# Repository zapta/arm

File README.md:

ARM PROJECTS
============

ARM PRO MINI 

Files: https://github.com/zapta/arm/tree/master/pro-mini

Documentation: https://github.com/zapta/arm/tree/master/pro-mini#arm-pro-mini

PHONE FINDER

Files: https://github.com/zapta/arm/tree/master/phone-finder

Documentation: https://github.com/zapta/arm/tree/master/phone-finder#phone-finder

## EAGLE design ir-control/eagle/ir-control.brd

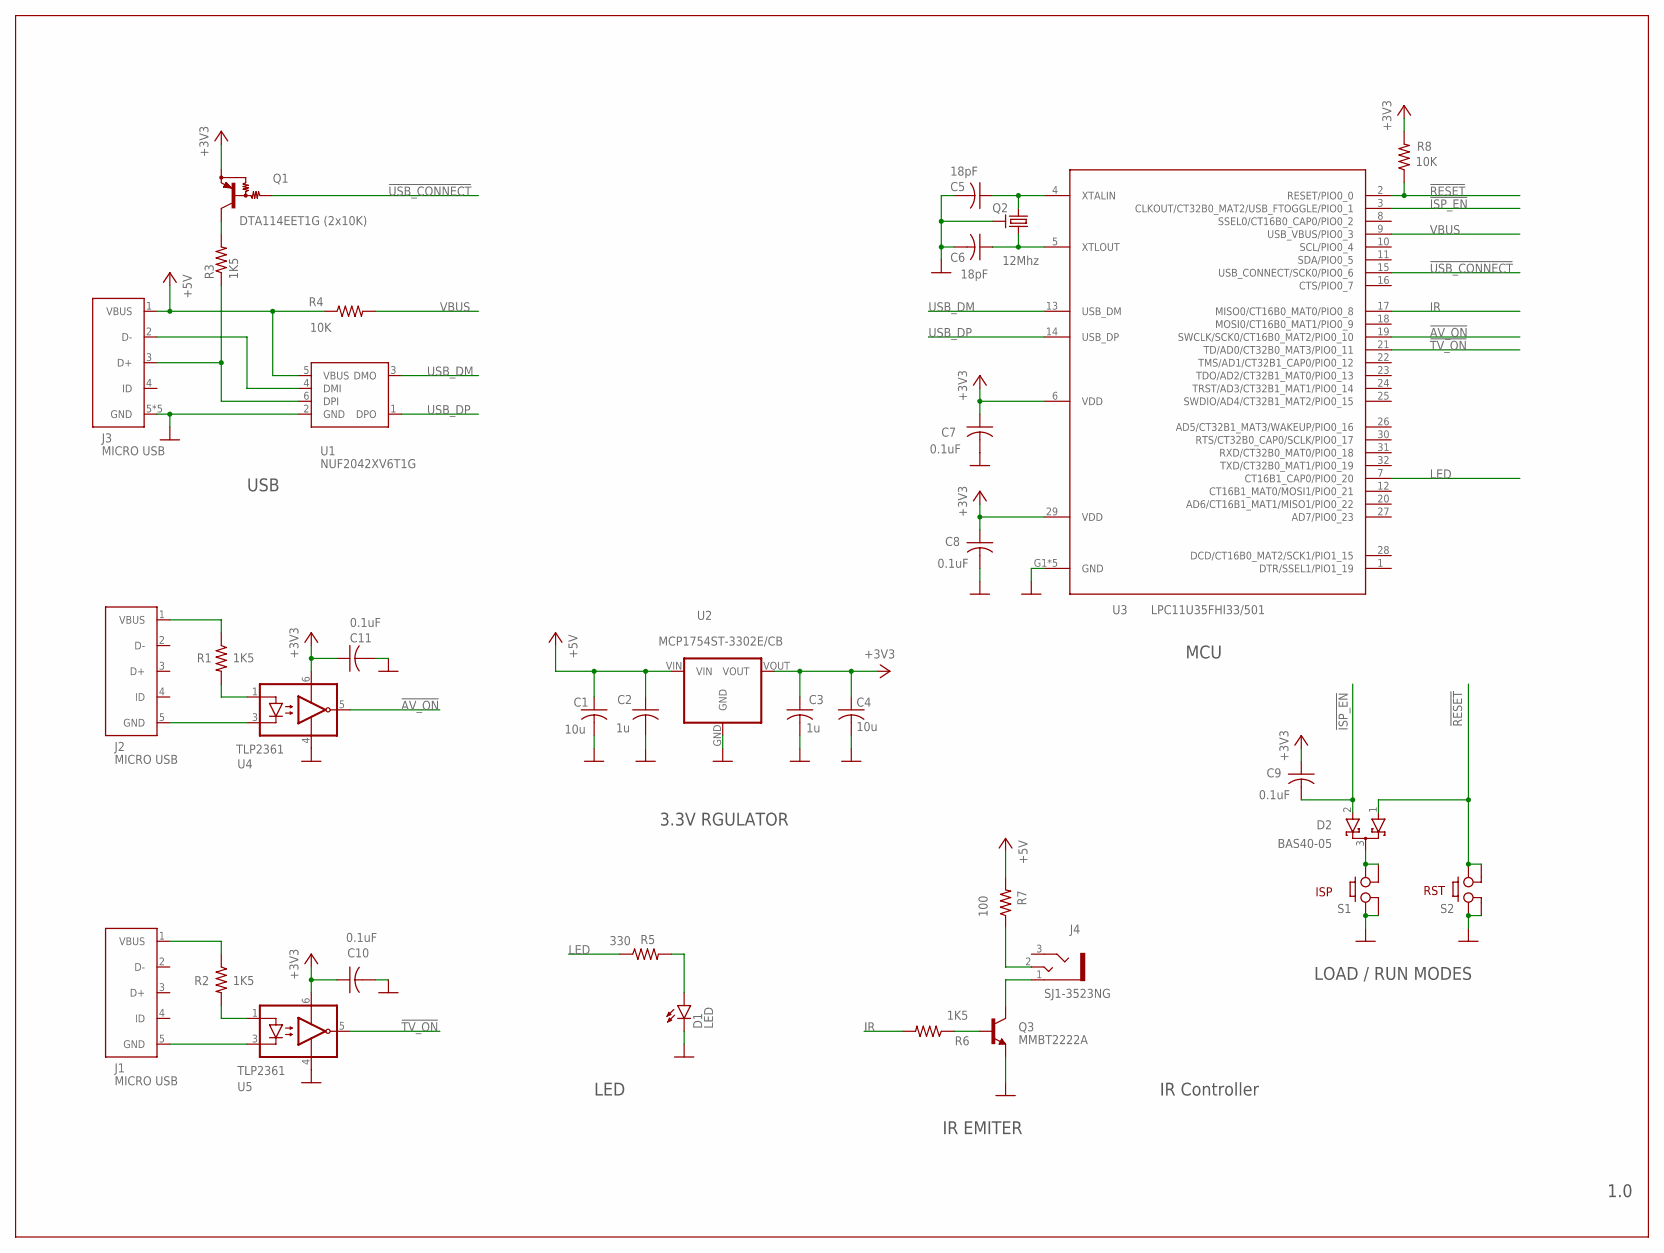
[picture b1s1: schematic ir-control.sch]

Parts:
C1, C4: 10u; C0805K
C2, C3: 1u; C0603K
C5, C6: 18pF; C0402K
C7, C8, C9, C10, C11: 0.1uF; C0402K
D1: LED
D2: BAS40-05; SOT23
J1, J2, J3: MICRO USB; USB-MICRO
J4: SJ1-3523NG; JACK
Q1: DTA114EET1G (2x10K); SC75-BEC
Q2: 12Mhz; CRYSTAL
Q3: MMBT2222A; SOT23
R1, R2, R3, R6: 1K5; R0402
R4, R8: 10K; R0402
R5: 330; R0402
R7: 100; R0402
S1: CKN10502CT-ND; PUSH_BUTTON
S2: PUSH-BUTTON; PUSH_BUTTON
U1: NUF2042XV6T1G; SOT-563
U2: MCP1754ST-3302E/CB; SOT-23A
U3: LPC11U35FHI33/501; HVQFN33-5MM
U4, U5: TLP2361; SO6

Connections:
!AV_ON: U3.19 (SWCLK/SCK0/CT16B0_MAT2/PIO0_10), U4.5 (OUT)
!ISP_EN: C9.2, D2.2 (A2), U3.3 (CLKOUT/CT32B0_MAT2/USB_FTOGGLE/PIO0_1)
!RESET: D2.1 (A1), R8.1, S2.B1, S2.B1P (B1), S2.B2, S2.B2P (B2), U3.2 (RESET/PIO0_0)
!TV_ON: U3.21 (TD/AD0/CT32B0_MAT3/PIO0_11), U5.5 (OUT)
!USB_CONNECT: Q1.B, U3.15 (USB_CONNECT/SCK0/PIO0_6)
+3V3: C3.1, C4.1, C7.1, C8.1, C9.1, C10.1, C11.1, Q1.E, R8.2, U2.VOUT, U3.6 (VDD), U3.29 (VDD), U4.6 (VCC), U5.6 (VCC)
+5V: C1.1, C2.1, J3.1 (VBUS), R4.1, R7.2, U1.5 (VBUS), U2.VIN
GND: C1.2, C2.2, C3.2, C4.2, C5.2, C6.2, C7.2, C8.2, C10.2, C11.2, D1.K (C), J3.5 (GND), J3.G1 (GND), J3.G2 (GND), J3.G3 (GND), J3.G4 (GND), Q2.2 (GND), Q2.4 (GND), Q3.2 (E), S1.A1, S1.A1P (A1), S1.A2, S1.A2P (A2), S2.A1, S2.A1P (A1), S2.A2, S2.A2P (A2), U1.2 (GND), U2.GND, U3.G1 (GND), U3.G2 (GND), U3.G3 (GND), U3.G4 (GND), U3.TAB (GND), U4.4 (GND), U5.4 (GND)
IR: R6.2, U3.17 (MISO0/CT16B0_MAT0/PIO0_8)
LED: R5.1, U3.7 (CT16B1_CAP0/PIO0_20)
unnamed: C5.1, Q2.3 (2), U3.4 (XTALIN)
unnamed: J2.1 (VBUS), R1.1
unnamed: C6.1, Q2.1, U3.5 (XTLOUT)
unnamed: Q3.1 (B), R6.1
unnamed: Q1.C, R3.2
unnamed: J3.3 (D+), R3.1, U1.6 (DPI)
unnamed: J1.1 (VBUS), R2.1
unnamed: J4.1, Q3.3 (C)
unnamed: J4.2, R7.1
unnamed: J2.5 (GND), U4.3 (C)
unnamed: J1.5 (GND), U5.3 (C)
unnamed: J3.2 (D-), U1.4 (DMI)
unnamed: R2.2, U5.1 (A)
unnamed: D1.A, R5.2
unnamed: R1.2, U4.1 (A)
unnamed: D2.3 (C), S1.B1, S1.B1P (B1), S1.B2, S1.B2P (B2)
USB_DM: U1.3 (DMO), U3.13 (USB_DM)
USB_DP: U1.1 (DPO), U3.14 (USB_DP)
VBUS: R4.2, U3.9 (USB_VBUS/PIO0_3)

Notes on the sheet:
IR Controller
1.0
USB
MCU
ISP
RST
3.3V RGULATOR
LOAD / RUN MODES
LED
IR EMITER

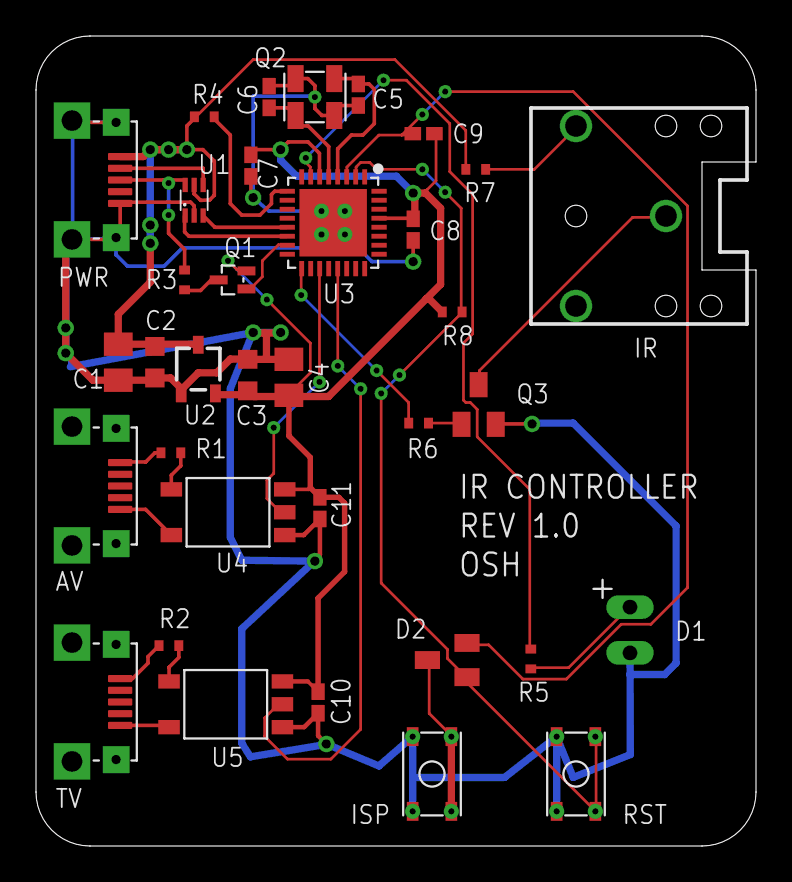
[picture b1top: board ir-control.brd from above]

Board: 2 copper layers, 40.0 x 45.0 mm, 35 parts (0 on the bottom side), 29 nets.

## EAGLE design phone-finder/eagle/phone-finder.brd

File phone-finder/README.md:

ARM PRO MINI
============

### OVERVIEW

Phone Finder is simple system that allows familty members to locate their cell phones.
The system works with an arbitrary number of Amazon Dash buttons that are placed 
in key locations such as near the exit door. When a Dash button is pressed, the system
dials the phone number that associated with that button, causing the respective cell
phone to ring.

The system uses a Phone Finder box that bridges between the Wifi connections from
the Dash buttons and the phone landline cord. The Phone Finder box acts as a Wifi 
access point that accepts Wifi connections directly from the Dash buttons and does
no require a local Wifi network or a connection to the internet.

[Schematic (PDF)](https://github.com/zapta/arm/blob/master/phone-finder/eagle/phone-finder-schematic.pdf)

This design is in the public domain and is provided AS IS. I am not an electronic or telephony engineer. All source files including eagle, LPCXpresso project, C++ source files and openscad 3D model source files are included.

<br>

### Design notes (assorted order)

* The PCB include an ARM mcu, a Wifi module and a phone line dialer. 
* The MCU design is based on the Arm Pro Mini. 
* The firmware is mbed based and was developed using NPX LPCXpresso (see ARM Pro Mini documentation)
* Loading the firmaware is done via the USB connector, similar to ARM Pro Mini.
* The enclosure and the LED mount are 3D printed. STL files and openscad source files are availabe here.
* To change the phone numbers you will need change the source files and build. Currntly there is no soft EEPROM based configuration.
* The DTFM is generated using two 16 bit counters of the ARM MCU. They generate square waves that are filtered out by a simple RC filter, the coupling transformer and the phone line itself.
* For simplicty, the coupling transformer was not decoupled from DC on both its primary and secondary. Howerver, it seems to work well.
* When assembling the PCB, the orientation of the transformer does matter. Make sure the primary is at the PCB side marked with 'P'.
* If you want to experiment talking directly to the wifi module, build and load the wifi-serial project. This will make the MCU acting as a USB to serial (CDC) adapter.
* For antenna I just soldered a 2$ AWG solid wire (strip at the end for the solder joint). If you want to experiment with different antennas, you can use the wifi module's s/n figure to compare configurations (use the serial-wifi firmware above).
* The PCB is attached to the enclosure base using Scotch Mounting Tape.
* The firmware comes with the default AP SSID 'dashrx' and the password 'dashdash' (password must have at least 8 chars). Change the firmware to customize.
* To make a button connecting to the AP, first set it with a real wifi AP connected to the internet. Set its SSID and password to the ones you want to use, and perform the Amazon Dash button setting using that real AP. Abort the process at the point where you need to select a product. Make sure to change the SSID of the real AP to other than your SSID of choice such that it doesn't interfer with the phone finder.
* Once your button(s) connect successuly to your phone finder (connect the USB connector to a computer, the phone finder acts as a  CDC serial port and dumps diagnostic data), add the mac address of those buttons to the button table in the firmware. 

<br>

If I will find time, I plan to design a lower cost version of the Phone Finder, replacing the ARM mcu and Wifi Module with an ESP8266/Arduino.

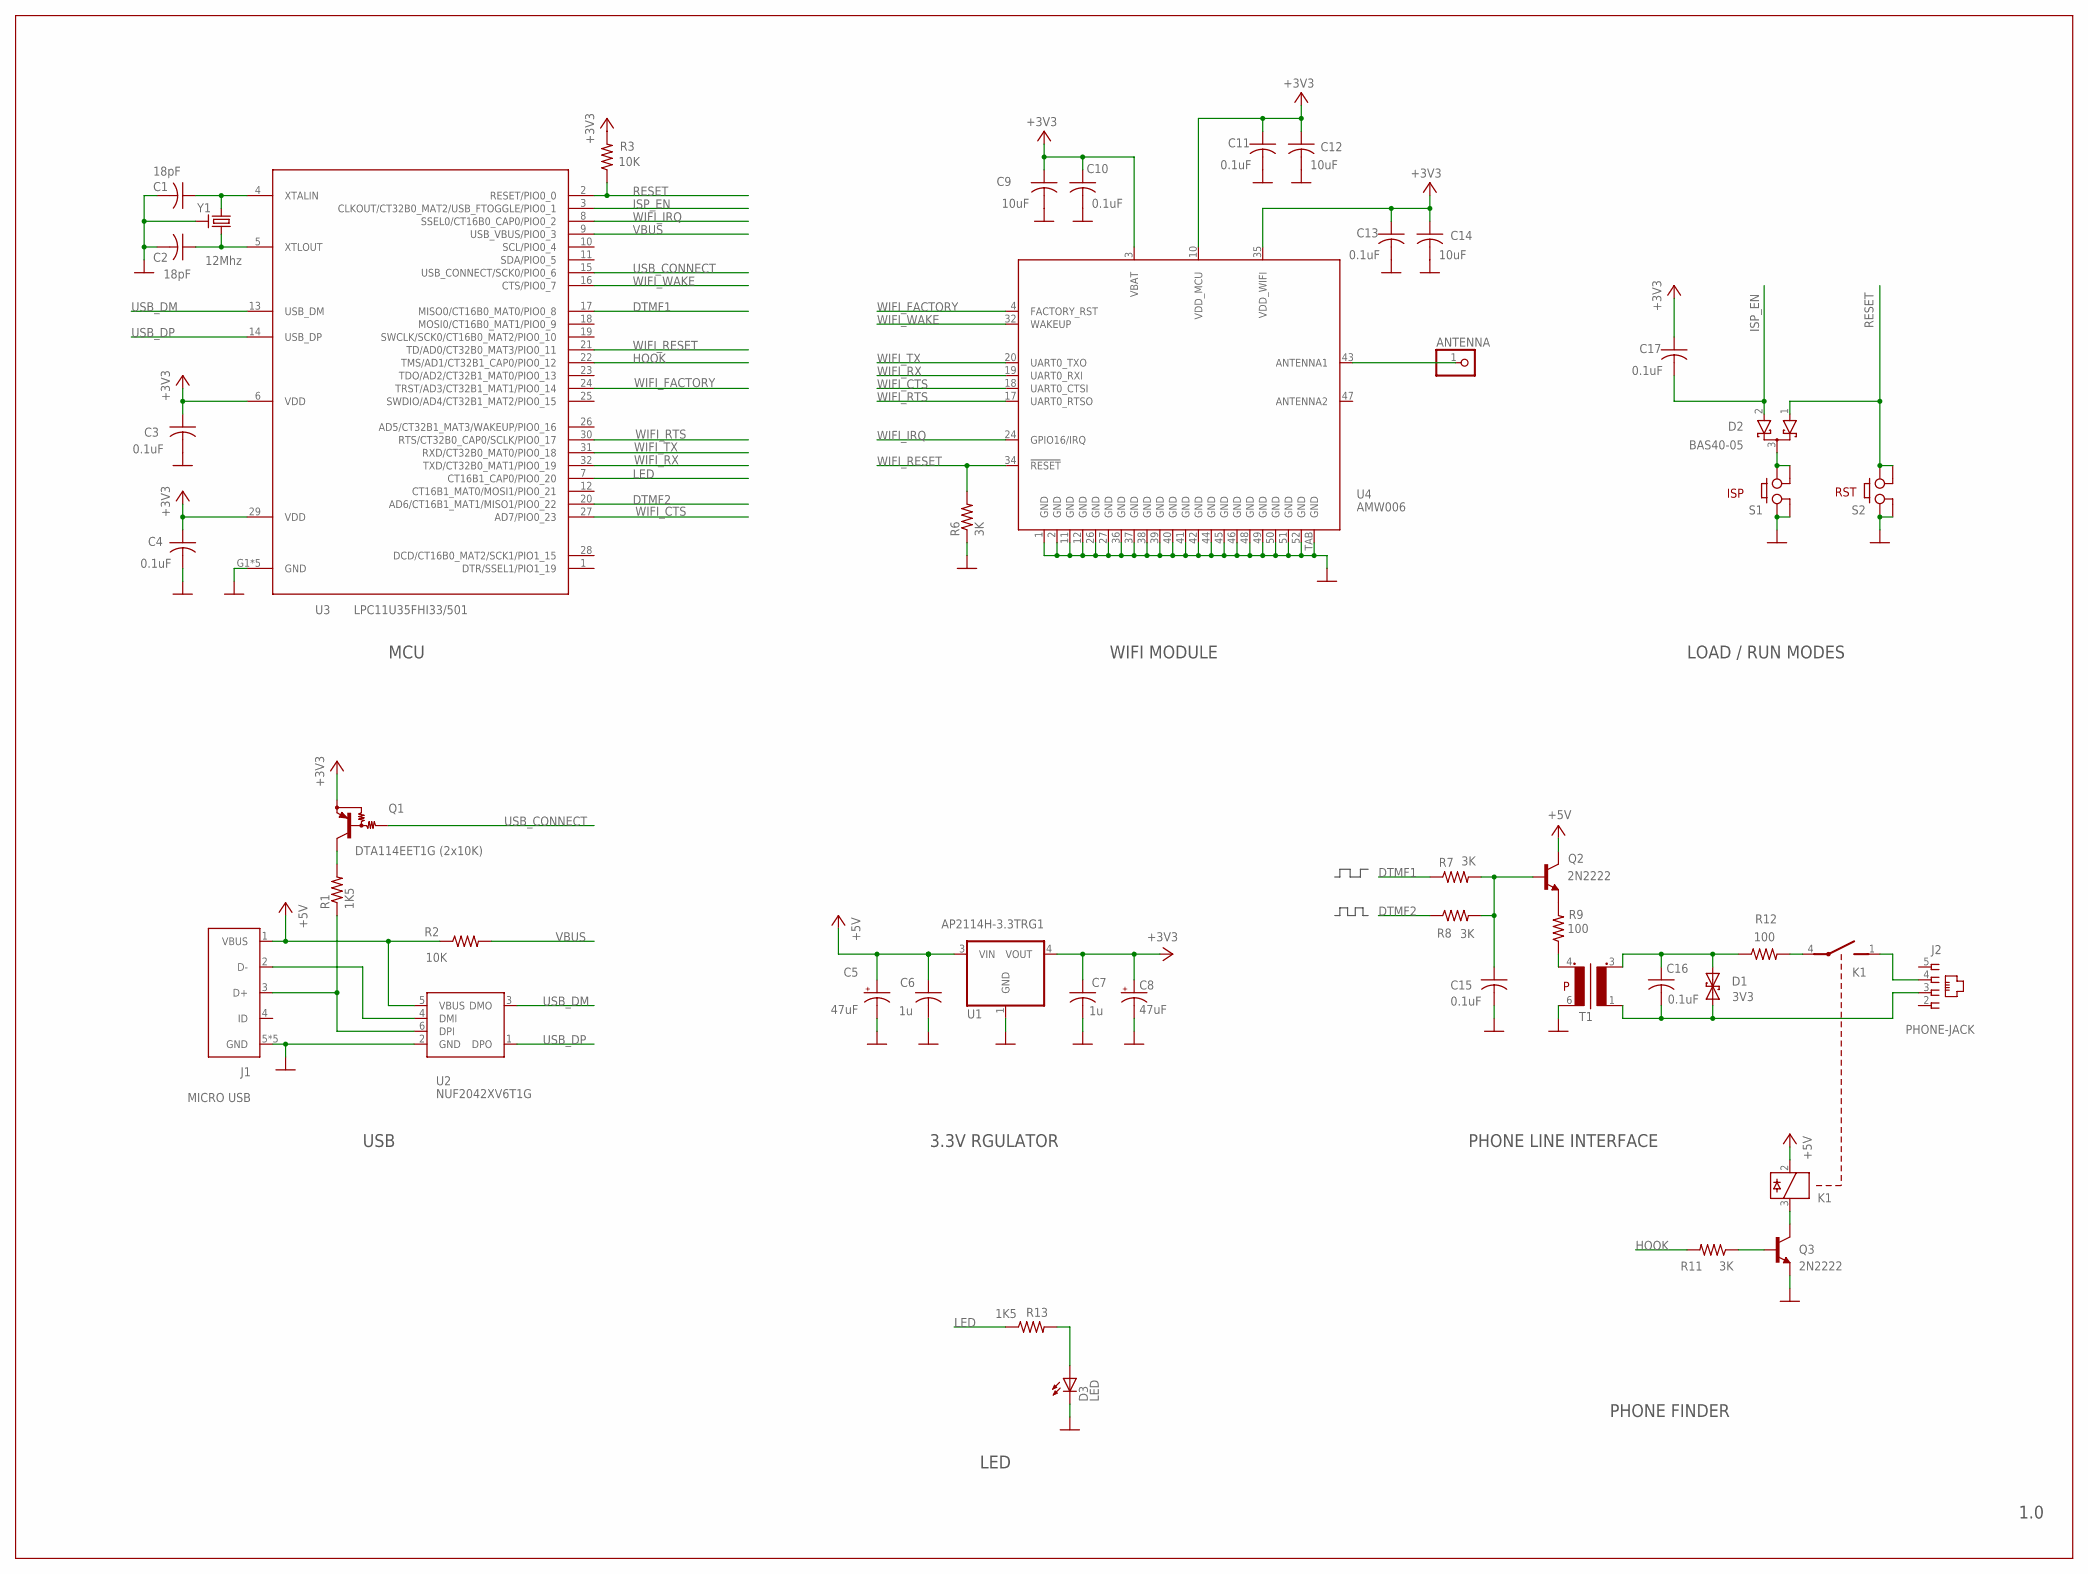
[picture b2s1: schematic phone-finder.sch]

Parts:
ANTENNA: PINHD-1X1
C1, C2: 18pF; C0402K
C3, C4, C10, C11, C13, C15, C16, C17: 0.1uF; C0402K
C5, C8: 47uF; UD-6,3X5,8_NICHICON
C6, C7: 1u; C0603K
C9, C12, C14: 10uF; C0805K
D1: 3V3; DZ-0402
D2: BAS40-05; SOT23
D3: LED
J1: MICRO USB; USB-MICRO
J2: PHONE-JACK
K1: RELAY
Q1: DTA114EET1G (2x10K); SC75-BEC
Q2, Q3: 2N2222; SOT23
R1, R13: 1K5; R0402
R2, R3: 10K; R0402
R6, R7, R8, R11: 3K; R0402
R9, R12: 100; R0805
S1, S2: PUSH-BUTTON; PUSH_BUTTON
T1: TRANSFORMER
U1: AP2114H-3.3TRG1; SOT223
U2: NUF2042XV6T1G; SOT-563
U3: LPC11U35FHI33/501; HVQFN33-5MM
U4: AMW006; WIFI_MODULE
Y1: 12Mhz; CRYSTAL

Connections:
+3V3: C3.1, C4.1, C7.1, C8.+, C9.1, C10.1, C11.1, C12.1, C13.1, C14.1, C17.1, Q1.E, R3.2, U1.4 (VOUT), U3.6 (VDD), U3.29 (VDD), U4.3 (VBAT), U4.10 (VDD_MCU), U4.35 (VDD_WIFI)
+5V: C5.+, C6.1, J1.1 (VBUS), K1.2 (COIL-POS), Q2.3 (C), R2.1, U1.3 (VIN), U2.5 (VBUS)
DTMF1: R7.1, U3.17 (MISO0/CT16B0_MAT0/PIO0_8)
DTMF2: R8.1, U3.20 (AD6/CT16B1_MAT1/MISO1/PIO0_22)
GND: C1.2, C2.2, C3.2, C4.2, C5.-, C6.2, C7.2, C8.-, C9.2, C10.2, C11.2, C12.2, C13.2, C14.2, C15.2, D3.K (C), J1.5 (GND), J1.G1 (GND), J1.G2 (GND), J1.G3 (GND), J1.G4 (GND), Q3.2 (E), R6.1, S1.A1, S1.A1P (A1), S1.A2, S1.A2P (A2), S2.A1, S2.A1P (A1), S2.A2, S2.A2P (A2), T1.6 (P2), U1.1 (GND), U2.2 (GND), U3.G1 (GND), U3.G2 (GND), U3.G3 (GND), U3.G4 (GND), U3.TAB (GND), U4.1 (GND), U4.2 (GND), U4.11 (GND), U4.12 (GND), U4.26 (GND), U4.27 (GND), U4.36 (GND), U4.37 (GND), U4.38 (GND), U4.39 (GND), U4.40 (GND), U4.41 (GND), U4.42 (GND), U4.44 (GND), U4.45 (GND), U4.46 (GND), U4.48 (GND), U4.49 (GND), U4.50 (GND), U4.51 (GND), U4.52 (GND), U4.TAB (GND), Y1.2 (GND), Y1.4 (GND)
HOOK: R11.2, U3.22 (TMS/AD1/CT32B1_CAP0/PIO0_12)
ISP_EN: C17.2, D2.2 (A2), U3.3 (CLKOUT/CT32B0_MAT2/USB_FTOGGLE/PIO0_1)
LED: R13.1, U3.7 (CT16B1_CAP0/PIO0_20)
unnamed: C1.1, U3.4 (XTALIN), Y1.3 (2)
unnamed: ANTENNA.1, U4.43 (ANTENNA1)
unnamed: C2.1, U3.5 (XTLOUT), Y1.1
unnamed: K1.3 (COIL-NEG), Q3.3 (C)
unnamed: Q1.C, R1.2
unnamed: J1.3 (D+), R1.1, U2.6 (DPI)
unnamed: Q3.1 (B), R11.1
unnamed: Q2.2 (E), R9.2
unnamed: C16.1, D1.2, R12.1, T1.3 (S1)
unnamed: C16.2, D1.1, J2.3, T1.1 (S2)
unnamed: J2.4, K1.1 (S1)
unnamed: J1.2 (D-), U2.4 (DMI)
unnamed: D3.A, R13.2
unnamed: K1.4 (S2), R12.2
unnamed: D2.3 (C), S1.B1, S1.B1P (B1), S1.B2, S1.B2P (B2)
unnamed: R9.1, T1.4 (P1)
unnamed: C15.1, Q2.1 (B), R7.2, R8.2
RESET: D2.1 (A1), R3.1, S2.B1, S2.B1P (B1), S2.B2, S2.B2P (B2), U3.2 (RESET/PIO0_0)
USB_CONNECT: Q1.B, U3.15 (USB_CONNECT/SCK0/PIO0_6)
USB_DM: U2.3 (DMO), U3.13 (USB_DM)
USB_DP: U2.1 (DPO), U3.14 (USB_DP)
VBUS: R2.2, U3.9 (USB_VBUS/PIO0_3)
WIFI_CTS: U3.27 (AD7/PIO0_23), U4.18 (UART0_CTSI)
WIFI_FACTORY: U3.24 (TRST/AD3/CT32B1_MAT1/PIO0_14), U4.4 (FACTORY_RST)
WIFI_IRQ: U3.8 (SSEL0/CT16B0_CAP0/PIO0_2), U4.24 (GPIO16/IRQ)
WIFI_RESET: R6.2, U3.21 (TD/AD0/CT32B0_MAT3/PIO0_11), U4.34 (!RESET)
WIFI_RTS: U3.30 (RTS/CT32B0_CAP0/SCLK/PIO0_17), U4.17 (UART0_RTSO)
WIFI_RX: U3.32 (TXD/CT32B0_MAT1/PIO0_19), U4.19 (UART0_RXI)
WIFI_TX: U3.31 (RXD/CT32B0_MAT0/PIO0_18), U4.20 (UART0_TXO)
WIFI_WAKE: U3.16 (CTS/PIO0_7), U4.32 (WAKEUP)

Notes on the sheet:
PHONE FINDER
1.0
USB
MCU
ISP
RST
3.3V RGULATOR
LOAD / RUN MODES
WIFI MODULE
PHONE LINE INTERFACE
LED

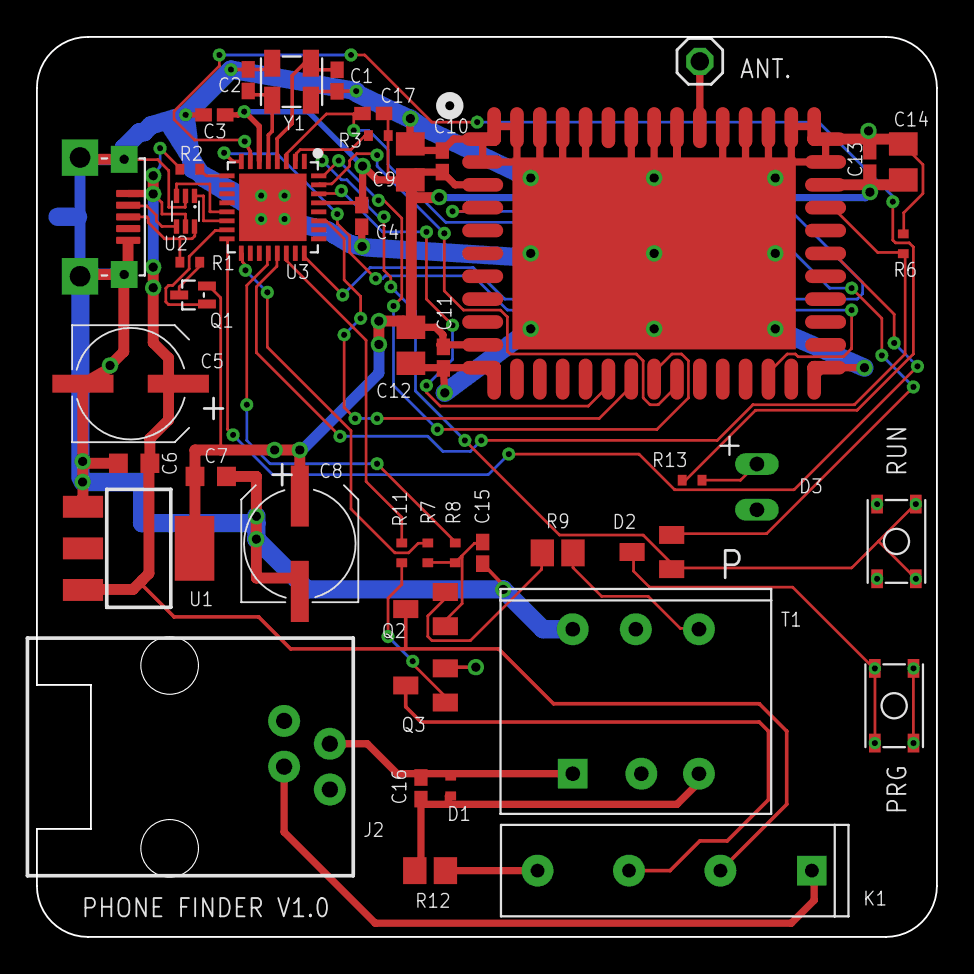
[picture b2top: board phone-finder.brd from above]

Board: 2 copper layers, 50.0 x 50.0 mm, 45 parts (0 on the bottom side), 38 nets.

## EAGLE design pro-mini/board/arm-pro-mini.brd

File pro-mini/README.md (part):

ARM PRO MINI
============

### OVERVIEW

ARM PRO MINI is a small barebone open source ARM M0 microcontroller board that is great for 
quick prototyping and as a starting point for your own ARM based custom designs. 
It was designed and named after the venerable Arduino Pro Mini and it is an excellent 
stepping stone for makers and hobbyists 'graduating' from Arduino to the ARM architecture.

[Schematic (PDF)](https://github.com/zapta/arm/blob/master/pro-mini/board/arm-pro-mini-schematic.pdf)

[BOM (CSV)](https://github.com/zapta/arm/blob/master/pro-mini/board/arm-pro-mini-bom.csv)

<br>
### Highlights

* Prototyping friendly. Compatible with standard soldieries breadboards and can be soldered to a standard 0.1” proto board.
* Straight forward barebone design. Customize for your own PCB design by selecting the portions of the circuit you need.
* Single package install of the free and fully feature IDE (NXP Eclipse/LPCXpresso).
* Zero software installation when using with the mbed.org online IDE.
* Full support of Windows, Mac OSX and Linux.
* Easy firmware upgrade using a file drag and drop. Programmers and adapters are not required, even if you are bringing up your own board!
* Supports optional debuggers (such as [LPC-LINK 2](http://www.digikey.com/short/7nr7n4)) for single stepping and full debugging capabilities.
* I/O library and a hello world example (with serial printing over USB, parallel port io, blinking LED, and timing).
* No-nonsense open source license (no commercial restrictions, sharing and attribution not required).

<br>
### Specification

Attribute | Value
:--------- | :-----
MCU | NXP ARM M0 LPC11U35FHI33/501
Memory | 64K flash, 8K RAM, 4K EEPROM
Speed | 48Mhz
Core voltage | 3.3V   (3.3V LDO included)
MCU Package | QFN 5x5mm, 0.5mm pitch, 32 pads + ground tab.
PCB dimensions | 1.5” x 0.775”  (38.1mm x 19.7mm)
PCB Layers | 2
PCB Thickness | 1mm recommended. (standard 1.6mm is also OK).
PCB file format | Eagle + PDF + Gerber files.
PCB rules | 6mil min trace, 7mil min spacing.
SMT Technology | 0402, QFN 0.5mm pitch.
Power options | USB, ext 3.3v, ext 16V max (with included 3.3V LDO) 
Header pins | 2x15 DIP, 0.7” row spacing. Access to all MCU's I/O pins.
USB Connector | Micro B
Debugger Connector | SWD 2x5 pin header, 0.5” pitch
Crystal | 12Mhz (for 48Mhz MCU operation).
LEDS | Power (blue), USB status (green), Application (red), 
Switches | Reset, ISP.
Recomanded IDE | NXP LPCXpresso (eclipse based, free)

<br>
### Pinout Diagram

<br>
### Where To Get an ARM PRO MINI?
As of Jan 2014 I have a limited supply of free ARM PRO MINI samples that I am giving to established eevblog users.
Since the license of the ARM PRO MINI is very liberal (attribution and share alike not required, commercial mixing and cloning are ok and free) it is likely that others will want to make them available to the public. If you want to list your offering here please let me know.

1. Make your own board. This will be a rewarding project, especially if you want to practice assembly of SMD boards. The complete BOM including digikey part numbers is available in the repository. You can order the PCB from OSH PARK by uploading the Eagle .brd file (~$6 per three boards). Mylar stencils are available from OSH STENCILS (I prefer the 5mil over the 3mil ones) and the board will be ready to use once it come out of your toaster oven (no need to program a bootloader). Make sure to have a decent magnifier glass for visutal inspection of the soldering and is you documented your build process let me know and I will mention it here. See more details below.

2. TBD.

<br>
### Quick Start 1 - Uploading a Compiled Program

This section will teach you how to load new firmware on your board. It is done by switching the board to the USB/ISP virtual disk mode and copying the new binary file.

1. Connect the ARM PRO MINI board to a USB port of a Max OSX, Linux or Windows computer.
2. Restart board in ISP mode by pressing the ISP button  (note: older versions require releasing the RST button while the ISP button is pressed).
3. The ARM PRO MINI will mount itself on your computer as an external disk with a single file named firmware.bin.
4. Copy one of the two provided hello world image files over the *firmware.bin* file. Note: on Mac OSX drag and drop does not work, instead using the cp shell command: *cp hello_world_fast_blink.bin "/Volumes/CRP DISABLD/firmware.bin"*
5. Press the RST button of the ARM PRO MINI to restart it in the RUN mode. The image file you just loaded should start running and the red LED on the ARM PRO MINI should blink.
6. Repeat the process with the other image file *hello_world_slow_blink.bin*  and notice how the blinking rate changes.

For more information about the USB bootloader see NXP's [application note AN11305](resources/lpc_bootloader/AN11305v.1.pdf).

<br>
### Quick Start 2 - Using the USB/Serial port.

This section will teach you how to view on your computer seial data output from the ARM PRO MINI. It is useful for example to communicate with a program running on the ARM PRO MINI or to debug a program you write using print messages.

1. Load and run a hello world image file as described above. Make sure the red LED blinks.
2. Identify the serial port on your computer. 
    * **Mac OSX:**  run _ls /dev/\*usb\*_, the port name looks like */dev/cu.usbmodemNXP-71*.
    * **Linux:** diff the output of the command _ls /dev/\*_ with and without the ARM PRO MINI 
      connected and look for a port that appears only when
      the ARM PRO MINI is connected. The serial port our linux test box is called */dev/ttyACM0* and is also availal with 
      two other name under the */dev/serial* directory.
    * **Windows:** (by Xenon Photon from the eevblog forums) 
      Identify the serial port on your computer: Open device manger, under "Ports(COM & LPT)" search for "LPC USB VCom Port (COMx)" 
      where x is the com port number.  
3. Use a terminal emulator to print the text received on the serial port you identified above.
    * **Mac OSX:** run the command *cat <port_name>*. For example *cat /dev/cu.usbmodemNXP-71*.
    * **Linux:** run the command *cat <port_name>*. For example *cat /dev/ttyACM0*.
    * **Windows:** (by Xenon Photon from the eevblog forums)
      Use a terminal emulator to print the text received on the serial port you identified above: 
      Download any terminal emulator, for example Tera Term http://en.sourceforge.jp/projects/ttssh2/releases/. 
      Select the com port of your device and click OK.
      Windows will install the required drive automatically via the internet. if the device was not recognized then 
      download the driver from here: http://www.lpcware.com/content/nxpfile/lpcxpresso-link2-usb-driver-package

The output will look like this:
~~~
...
Hello world: 4, 1500177
Hello world: 5, 1800178
Hello world: 6, 2100178
Hello world: 7, 2400178
Hello world: 8, 2700177
...
~~~

<br>
### Quick Start 3 - Installing the LPCXpresso IDE and compiling Hello World.

This section will teach you how to install the NXP LPCXpresso IDE and how to setup and compile a project for the ARM PRO MINI.

1. Download and Install the LPCXpresso IDE as described here http://www.lpcware.com/lpcxpresso/download. (this tutorial verified with LPCXpresso V7.3.0 on Mac OSX 10.9.5).
2. Copy the project directory https://github.com/zapta/arm/tree/master/pro-mini to your computer (e.g. by cloning the github repository or by extracting the zip file https://github.com/zapta/arm/archive/master.zip).
3. Import the *arm_pro_mini_lib* and *hellow_world* projects into LPCXpresso:
    * Select *File | Import... | General | Existing Projects into workspace* and then click *Next*
    * Select the archive file *arm_pro_min_getting_started.zip*, verify that the two projects *arm_pro_mini_lib* and *hello_world* are selected and then click *Finish*.
4. Build the hello world image file:
    * Right click on the *hello_world* project and select *Build Project*.
    * Expand the *hello_world* project and verify that the image file *hello_world.bin* created in the Debug directory.
7. Load the generated *hello_world.bin* image file to the ARM PRO MINI board using the USB/ISP bootloader as described above.
8. Modify the file *src/hello_file.cpp* in the *hellow_world* project (e.g. change the value of *kCycleTimeUsecs*), rebuild and load the file and verify that your changes took effect.

<br>

<br>
### Automatic Build/Download Using LPCXpresso
This section explains how to setup LPCXpresso to automate the process of building your project and downloading the generated .bin file to your ARM PRO MINI board via the USB/ISP bootloader (rather copying the .bin file manually as explained eariler). This is done by setting up the provided *arm_pro_mini_lib/tools/copy_bin_to_usb_isp.sh* script as an external LPCXpresso tool.

**New**: Batch file for Windows has been added. The existing script was tested on Mac OSX and should work also on Linux.

1. In LPCXpresson, open *Run | External Tools | External Tools Configuration ...*.
2. Add a new launch configuration.
3. Set the name of the new launch configuration to *USB_ISP*.
3. In the *Main* tab set the Location field to *${workspace_loc:/arm_pro_mini_lib/tools/copy_bin_to_usb_isp.sh}* on Mac; or to *${workspace_loc:/arm_pro_mini_lib/tools/copy_bin_to_usb_isp.bat}* on windows. Set the Arguments field to *${project_name} ${project_loc} ${config_name:${project_name}}*
4. In the *Common* tab check *External Tools* to display the external tool icon in the tool bar.
5. Click *Close*.
6. To build and download switch the ARM PRO MINI board to USB/ISP mode by pressing the ISP button (note: older versions of the board require release the RST button while the ISP button is pressed), then click on the *External Tool* icon and run USB/ISP. When the build and download are completed, reset your ARM PRO MINI board to start the new program you just downloaded.

<br>

<br>

<br>
### The ARM PRO MINI Library
This library includes everything you will need to program the ARM PRO MINI. It includes simplified low level chip and board definitions (based on LPCOPEN) as well as original code that support serial over USB/CDC, passive timers, digital pin I/O and more. It is installed in LPCXpresso as a library project which the hello world project (and in the future your own progrmas) depends on. The depenency is defined in the hello world LPCXpresso project such that compiling the hello world project also compiles the library if needed. 

<br>
### The Hello World Example
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
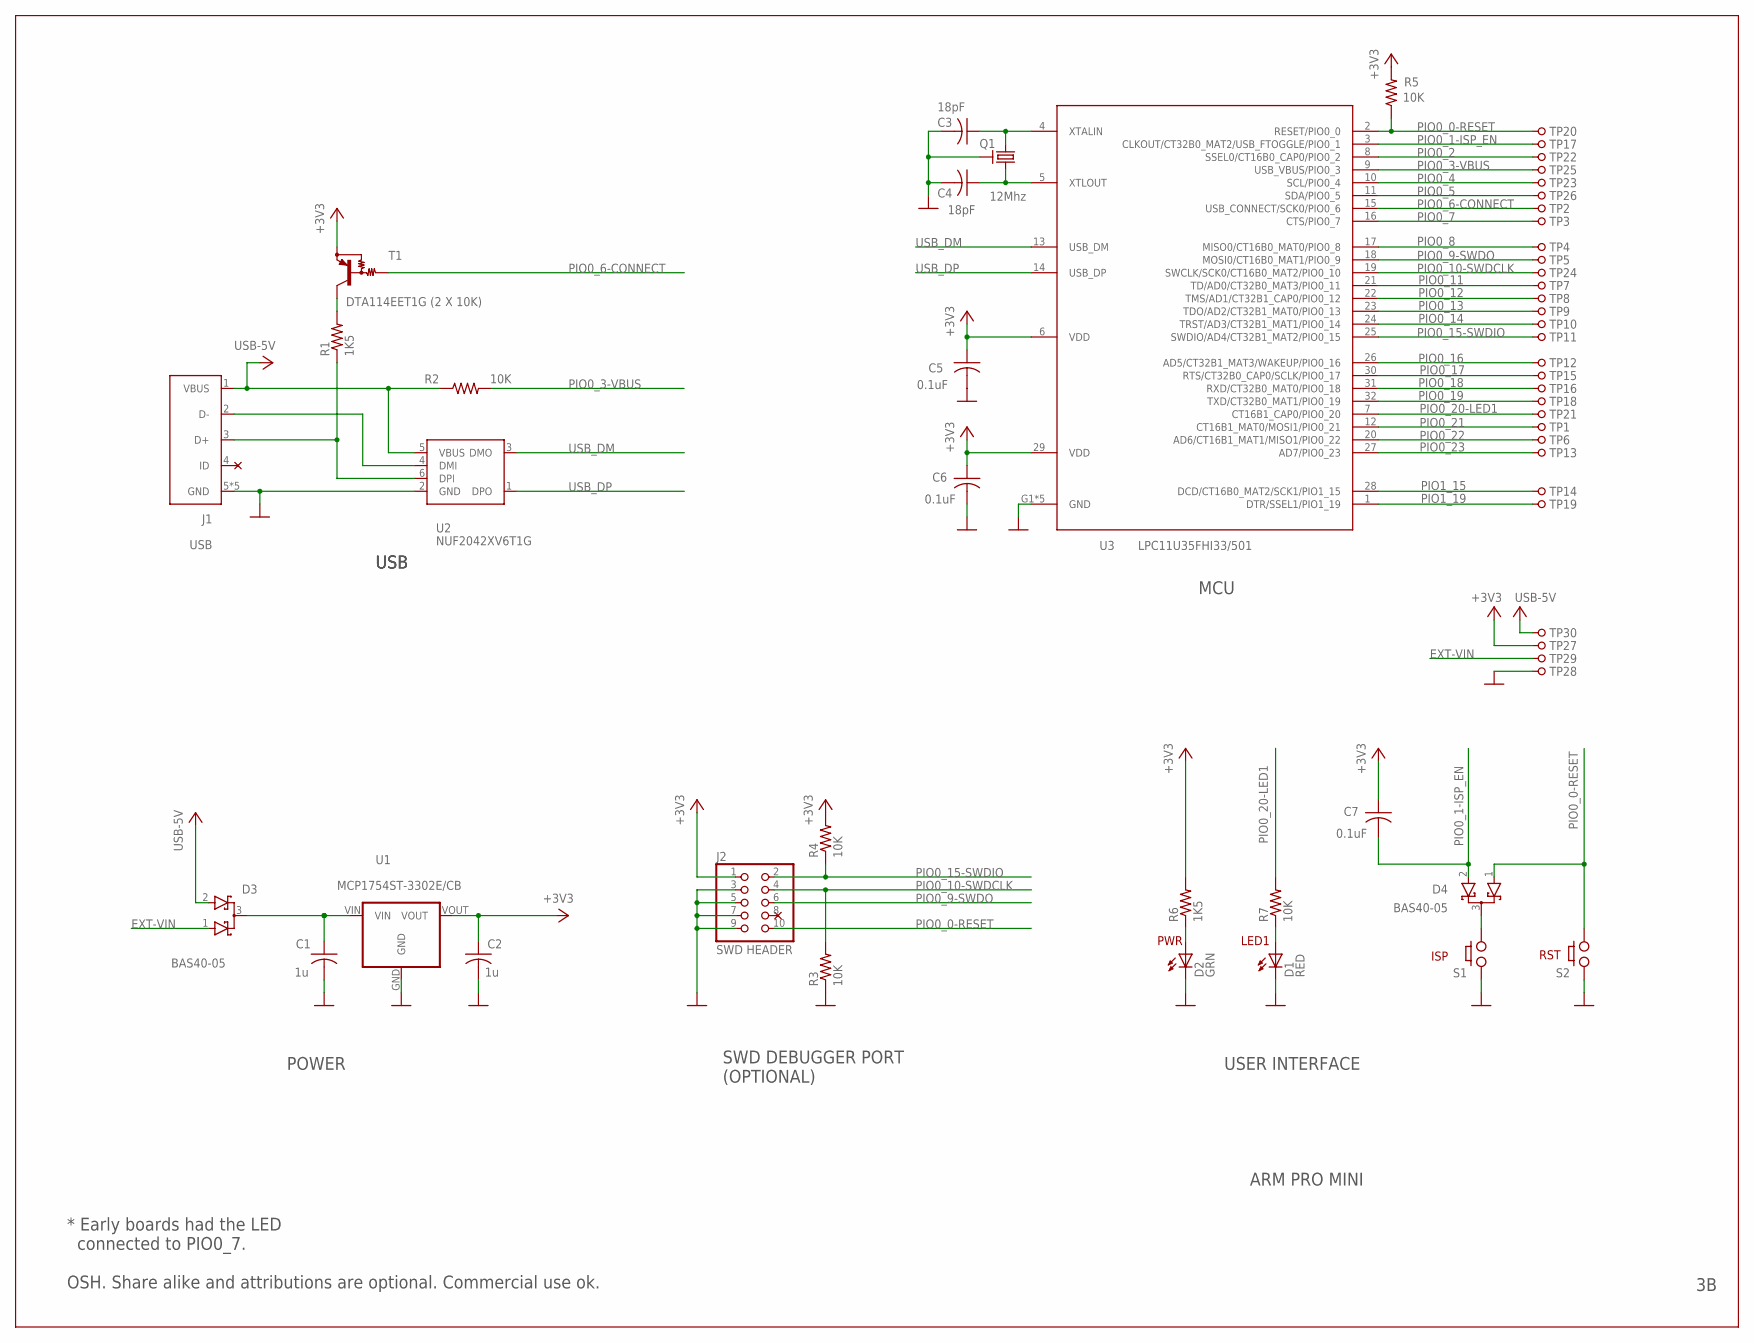
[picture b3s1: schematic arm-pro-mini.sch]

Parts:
C1, C2: 1u; C0603K
C3, C4: 18pF; C0402K
C5, C6, C7: 0.1uF; C0603K
D1: RED; LED0603
D2: GRN; LED0603
D3, D4: BAS40-05; SOT23
J1: USB; USB-MICRO
J2: SWD HEADER; SWD-HEADER
Q1: 12Mhz; CRYSTAL
R1, R6: 1K5; R0402
R2, R3, R4, R5, R7: 10K; R0402
S1, S2: PUSH_BUTTON
T1: DTA114EET1G (2 X 10K); SC75-BEC
TP1, TP2, TP3, TP4, TP5, TP6, TP7, TP8, TP9, TP10, TP11, TP12, TP13, TP14, TP15, TP16, TP17, TP18, TP19, TP20, TP21, TP22, TP23, TP24, TP25, TP26, TP27, TP28, TP29, TP30: HDR1; 1X01
U1: MCP1754ST-3302E/CB; SOT-23A
U2: NUF2042XV6T1G; SOT-563
U3: LPC11U35FHI33/501; HVQFN33-5MM

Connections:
+3V3: C2.1, C5.1, C6.1, C7.1, J2.1, R4.2, R5.2, R6.2, T1.E, TP27.1, U1.VOUT, U3.6 (VDD), U3.29 (VDD)
EXT-VIN: D3.1 (A1), TP29.1
GND: C1.2, C2.2, C3.2, C4.2, C5.2, C6.2, D1.C, D2.C, J1.5 (GND), J1.G1 (GND), J1.G2 (GND), J1.G3 (GND), J1.G4 (GND), J2.3, J2.5, J2.7, J2.9, Q1.2 (GND), Q1.4 (GND), R3.1, S1.A1 (1), S1.A1P (1), S2.A1 (1), S2.A1P (1), TP28.1, U1.GND, U2.2 (GND), U3.G1 (GND), U3.G2 (GND), U3.G3 (GND), U3.G4 (GND), U3.TAB (GND)
unnamed: C3.1, Q1.3 (2), U3.4 (XTALIN)
unnamed: D2.A, R6.1
unnamed: C4.1, Q1.1, U3.5 (XTLOUT)
unnamed: J1.2 (D-), U2.4 (DMI)
unnamed: R1.2, T1.C
unnamed: D1.A, R7.1
unnamed: J1.3 (D+), R1.1, U2.6 (DPI)
unnamed: D4.3 (C), S1.B2 (2), S1.B2P (2)
unnamed: C1.1, D3.3 (C), U1.VIN
PIO0_0-RESET: D4.1 (A1), J2.10, R5.1, S2.B2 (2), S2.B2P (2), TP20.1, U3.2 (RESET/PIO0_0)
PIO0_1-ISP_EN: C7.2, D4.2 (A2), TP17.1, U3.3 (CLKOUT/CT32B0_MAT2/USB_FTOGGLE/PIO0_1)
PIO0_2: TP22.1, U3.8 (SSEL0/CT16B0_CAP0/PIO0_2)
PIO0_3-VBUS: R2.2, TP25.1, U3.9 (USB_VBUS/PIO0_3)
PIO0_4: TP23.1, U3.10 (SCL/PIO0_4)
PIO0_5: TP26.1, U3.11 (SDA/PIO0_5)
PIO0_6-CONNECT: T1.B, TP2.1, U3.15 (USB_CONNECT/SCK0/PIO0_6)
PIO0_7: TP3.1, U3.16 (CTS/PIO0_7)
PIO0_8: TP4.1, U3.17 (MISO0/CT16B0_MAT0/PIO0_8)
PIO0_9-SWDO: J2.6, TP5.1, U3.18 (MOSI0/CT16B0_MAT1/PIO0_9)
PIO0_10-SWDCLK: J2.4, R3.2, TP24.1, U3.19 (SWCLK/SCK0/CT16B0_MAT2/PIO0_10)
PIO0_11: TP7.1, U3.21 (TD/AD0/CT32B0_MAT3/PIO0_11)
PIO0_12: TP8.1, U3.22 (TMS/AD1/CT32B1_CAP0/PIO0_12)
PIO0_13: TP9.1, U3.23 (TDO/AD2/CT32B1_MAT0/PIO0_13)
PIO0_14: TP10.1, U3.24 (TRST/AD3/CT32B1_MAT1/PIO0_14)
PIO0_15-SWDIO: J2.2, R4.1, TP11.1, U3.25 (SWDIO/AD4/CT32B1_MAT2/PIO0_15)
PIO0_16: TP12.1, U3.26 (AD5/CT32B1_MAT3/WAKEUP/PIO0_16)
PIO0_17: TP15.1, U3.30 (RTS/CT32B0_CAP0/SCLK/PIO0_17)
PIO0_18: TP16.1, U3.31 (RXD/CT32B0_MAT0/PIO0_18)
PIO0_19: TP18.1, U3.32 (TXD/CT32B0_MAT1/PIO0_19)
PIO0_20-LED1: R7.2, TP21.1, U3.7 (CT16B1_CAP0/PIO0_20)
PIO0_21: TP1.1, U3.12 (CT16B1_MAT0/MOSI1/PIO0_21)
PIO0_22: TP6.1, U3.20 (AD6/CT16B1_MAT1/MISO1/PIO0_22)
PIO0_23: TP13.1, U3.27 (AD7/PIO0_23)
PIO1_15: TP14.1, U3.28 (DCD/CT16B0_MAT2/SCK1/PIO1_15)
PIO1_19: TP19.1, U3.1 (DTR/SSEL1/PIO1_19)
USB-5V: D3.2 (A2), J1.1 (VBUS), R2.1, TP30.1, U2.5 (VBUS)
USB_DM: U2.3 (DMO), U3.13 (USB_DM)
USB_DP: U2.1 (DPO), U3.14 (USB_DP)

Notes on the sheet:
ARM PRO MINI
MCU
USB
SWD DEBUGGER PORT (OPTIONAL)
ISP
RST
LED1
PWR
USER INTERFACE
POWER
OSH. Share alike and attributions are optional. Commercial use ok.
* Early boards had the LED connected to PIO0_7.

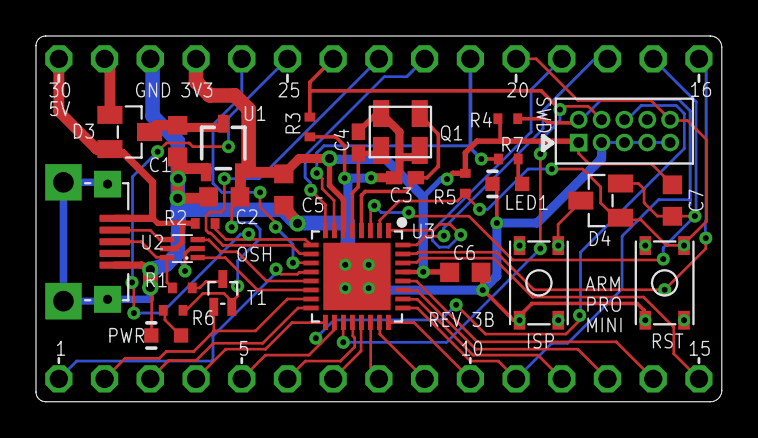
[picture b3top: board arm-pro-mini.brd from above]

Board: 2 copper layers, 38.1 x 20.3 mm, 57 parts (0 on the bottom side), 41 nets.

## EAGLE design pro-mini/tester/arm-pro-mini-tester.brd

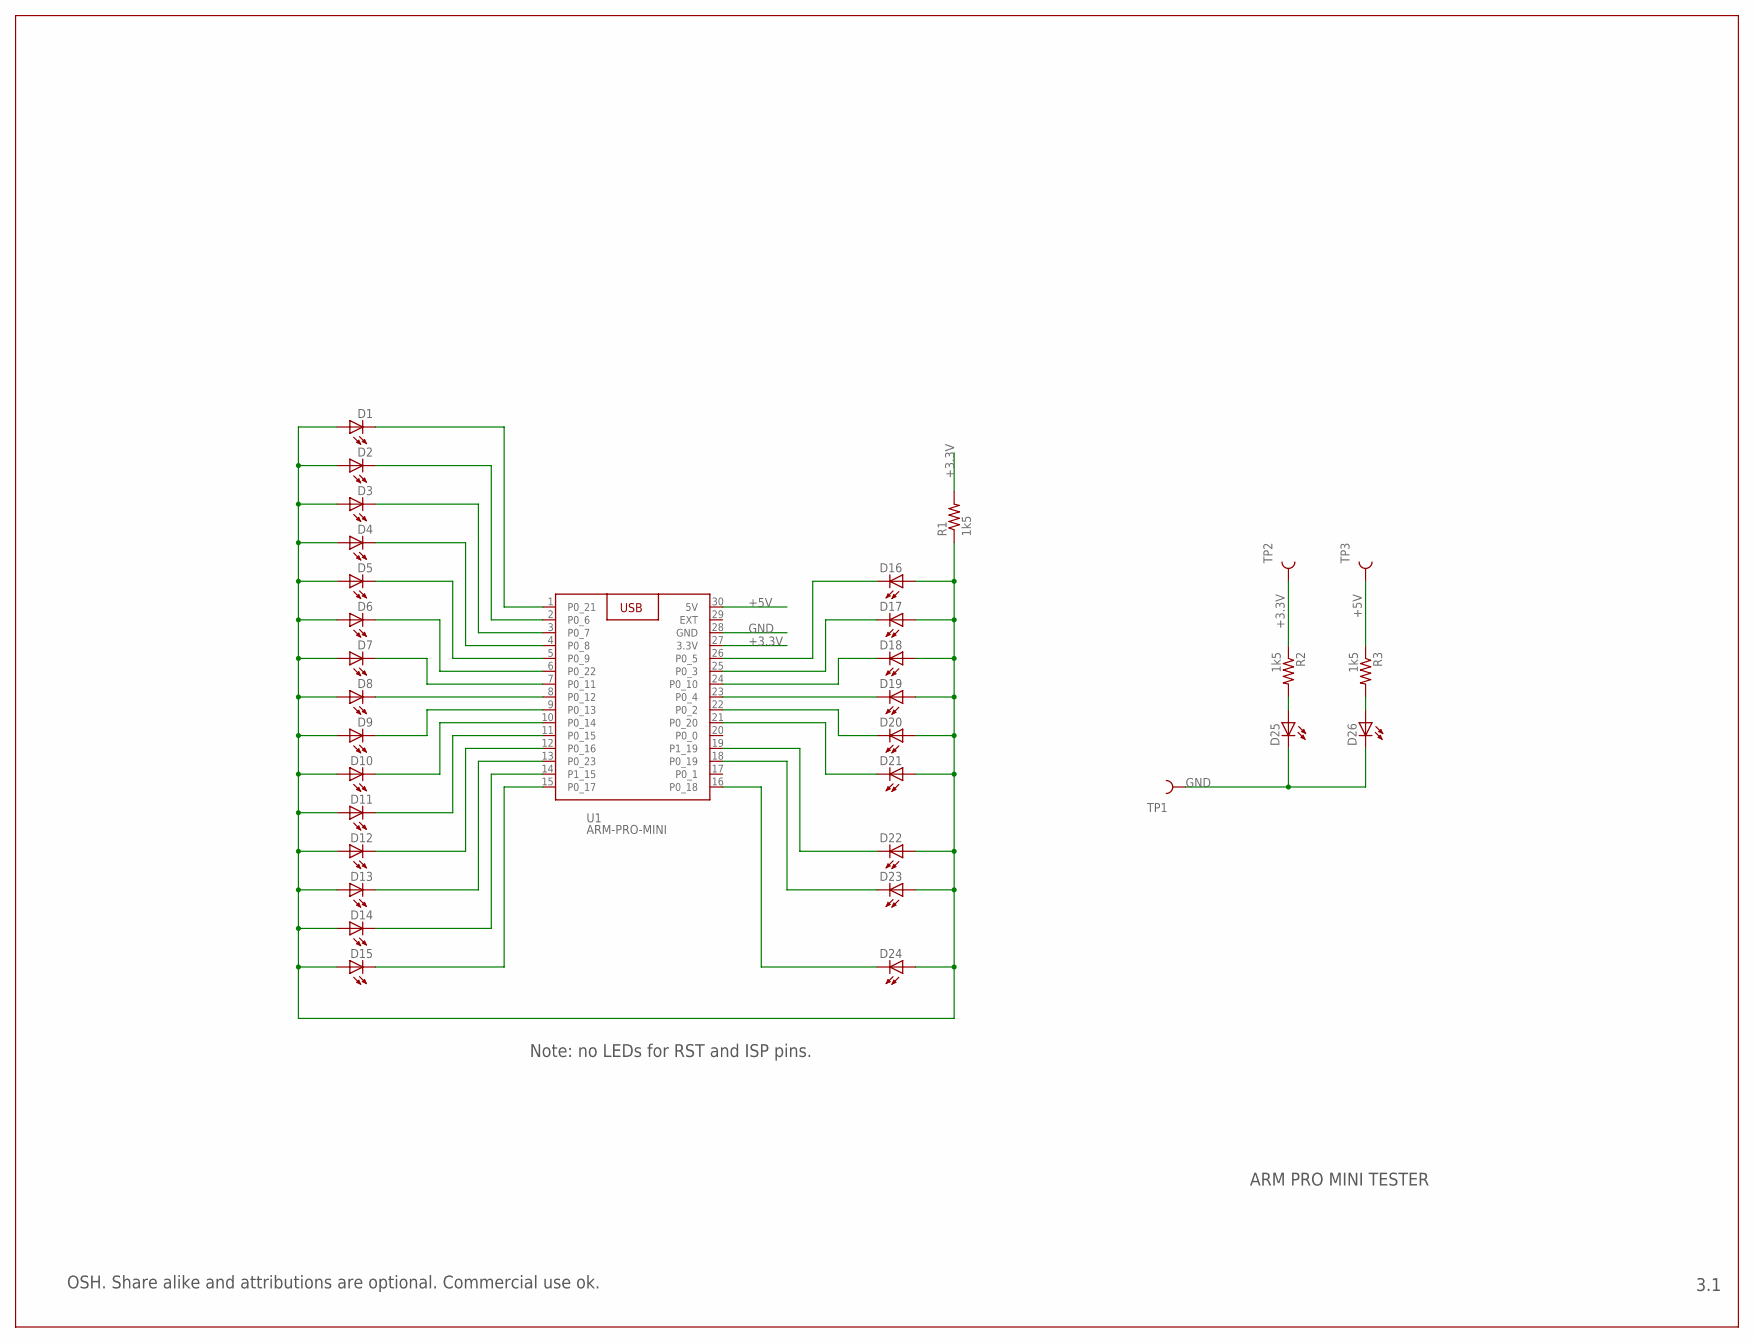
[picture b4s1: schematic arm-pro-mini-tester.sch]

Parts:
D1, D2, D3, D4, D5, D6, D7, D8, D9, D10, D11, D12, D13, D14, D15, D16, D17, D18, D19, D20, D21, D22, D23, D24, D25, D26: LED; LED0603
R1, R2, R3: 1k5; R0603
TP1, TP2, TP3: TEST-POINT
U1: ARM-PRO-MINI

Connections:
+3.3V: R1.2, R2.1, TP2.A, TP2.B, U1.27 (3.3V)
+5V: R3.1, TP3.A, TP3.B, U1.30 (5V)
GND: D25.C, D26.C, TP1.A, TP1.B, U1.28 (GND)
unnamed: D1.C, U1.1 (P0_21)
unnamed: D2.C, U1.2 (P0_6)
unnamed: D3.C, U1.3 (P0_7)
unnamed: D4.C, U1.4 (P0_8)
unnamed: D5.C, U1.5 (P0_9)
unnamed: D15.C, U1.15 (P0_17)
unnamed: D14.C, U1.14 (P1_15)
unnamed: D13.C, U1.13 (P0_23)
unnamed: D12.C, U1.12 (P0_16)
unnamed: D11.C, U1.11 (P0_15)
unnamed: D10.C, U1.10 (P0_14)
unnamed: D6.C, U1.6 (P0_22)
unnamed: D7.C, U1.7 (P0_11)
unnamed: D9.C, U1.9 (P0_13)
unnamed: D8.C, U1.8 (P0_12)
unnamed: D19.C, U1.23 (P0_4)
unnamed: D24.C, U1.16 (P0_18)
unnamed: D23.C, U1.18 (P0_19)
unnamed: D22.C, U1.19 (P1_19)
unnamed: D21.C, U1.21 (P0_20)
unnamed: D20.C, U1.22 (P0_2)
unnamed: D18.C, U1.24 (P0_10)
unnamed: D17.C, U1.25 (P0_3)
unnamed: D16.C, U1.26 (P0_5)
unnamed: D1.A, D2.A, D3.A, D4.A, D5.A, D6.A, D7.A, D8.A, D9.A, D10.A, D11.A, D12.A, D13.A, D14.A, D15.A, D16.A, D17.A, D18.A, D19.A, D20.A, D21.A, D22.A, D23.A, D24.A, R1.1
unnamed: D25.A, R2.2
unnamed: D26.A, R3.2

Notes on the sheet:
ARM PRO MINI TESTER
3.1
OSH. Share alike and attributions are optional. Commercial use ok.
Note: no LEDs for RST and ISP pins.

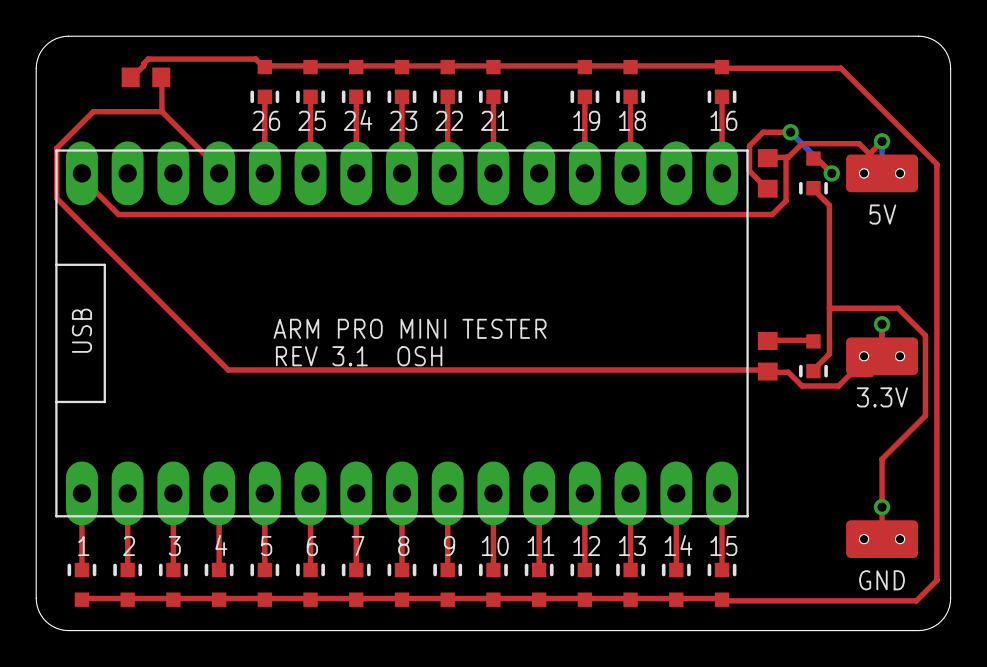
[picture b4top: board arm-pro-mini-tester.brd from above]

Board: 2 copper layers, 50.8 x 33.0 mm, 33 parts (0 on the bottom side), 30 nets.
